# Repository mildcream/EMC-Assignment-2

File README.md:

# Readme

## Smaller headline 

### Smallest headline

* list
* blabla 
* bReadme

## Smaller headline 

### Smallest headline

* list
* blabla 
* babla

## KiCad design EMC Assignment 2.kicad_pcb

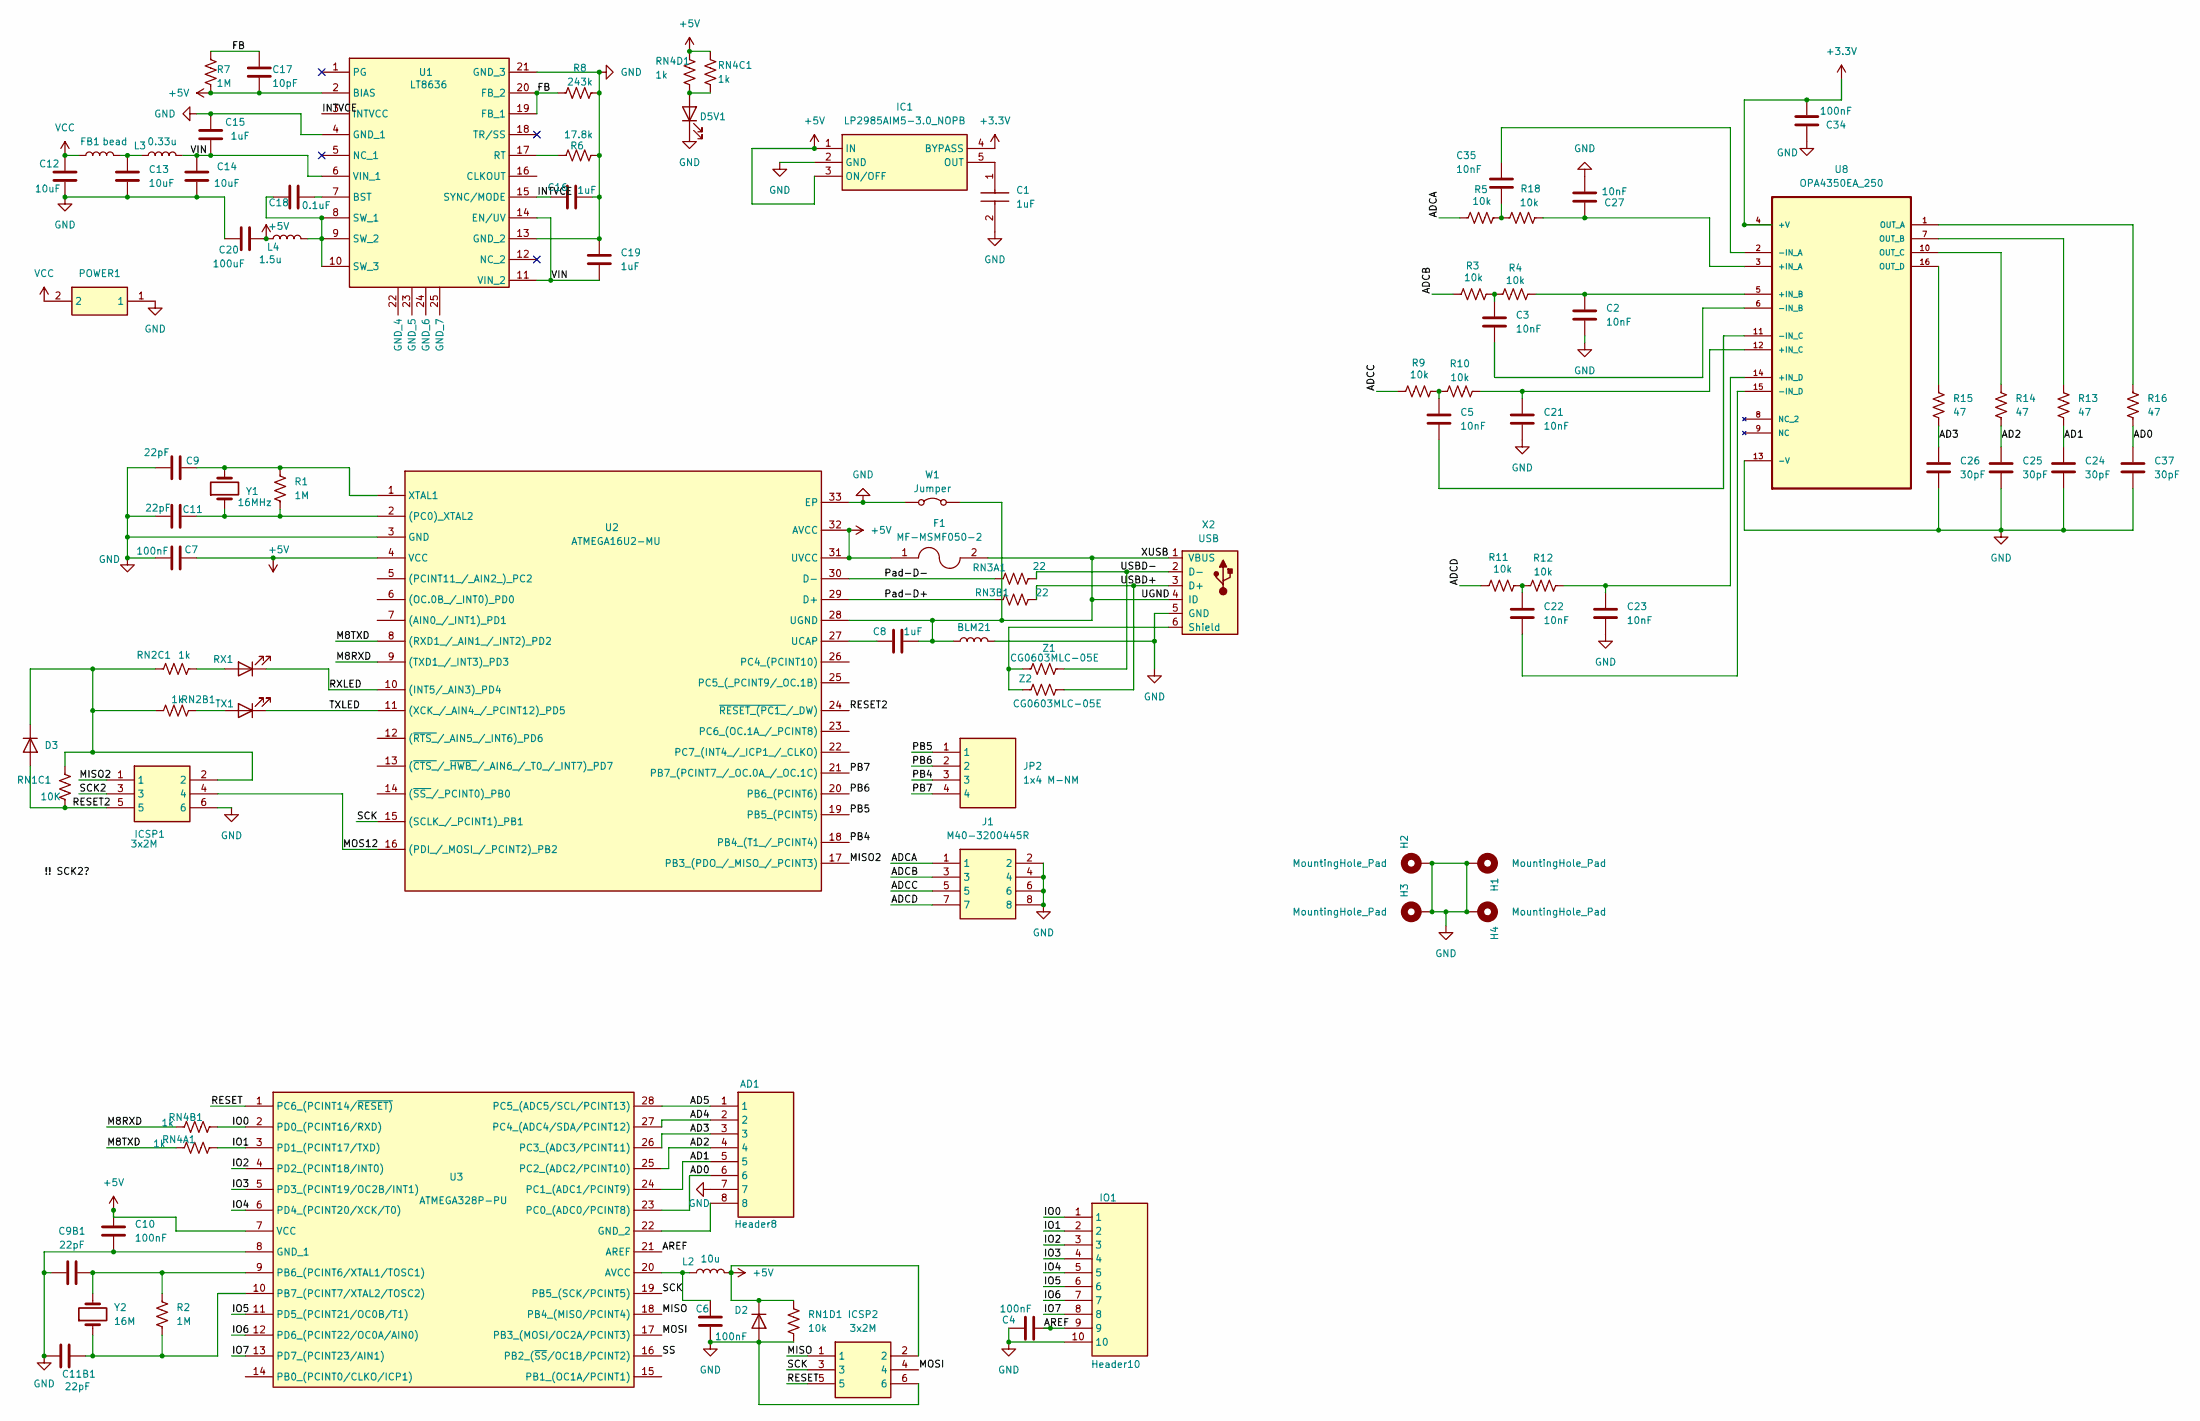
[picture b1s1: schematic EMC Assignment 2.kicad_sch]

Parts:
AD1: Header8; HDRV8W69P0X254_1X8_2032X251X1641P; Mouser Part Number 538-87891-0808
BLM21: L; BLM21AG102BH1J
C1: 1uF; C_0805_2012Metric; Mouser Part Number 581-0805ZC105KAZ2A
C2, C3, C5, C21, C22, C23, C27, C35: 10nF; C_0805_2012Metric
C4, C6, C7, C10: 100nF; C0805
C8, C15, C16, C19: 1uF; C0805
C9, C9B1, C11, C11B1: 22pF; C0805
C12, C13, C14: 10uF; C0805
C17: 10pF; C0805
C18: 0.1uF; C0805
C20: 100uF; C0805
C24, C25, C26, C37: 30pF; C_0805_2012Metric
C34: 100nF; C_0805_2012Metric
D2: 1N4148WT; D_SOD-523
D3: D; D_0805_2012Metric
D5V1: LED; LED_0805_2012Metric
F1: MF-MSMF050-2; FUSC4632X85N; Mouser Part Number 652-MF-MSMF050-2
FB1: bead; L_0805_2012Metric
H1, H2, H3, H4: MountingHole_Pad; MountingHole_2.1mm
IC1: LP2985AIM5-3.0_NOPB; SOT95P280X145-5N; Mouser Part Number 926-2985AIM53.0/NOPB
ICSP1, ICSP2: 3x2M; M225320305R; Mouser Part Number 855-M22-5320305R
IO1: Header10; SHDR10W64P0X250_1X10_2740X575X700P; Manufacturer_Part_Number B10B-XASK-1(LF)(SN)
J1: M40-3200445R; HUSSP8W30P100_2X4_400X320X365P; Mouser Part Number 855-M40-3200445R
JP2: 1x4 M-NM; RHDR4W70P0X254_1X4_1056X250X865P; Mouser Part Number 855-M20-7820446
L2: 10u; L_0805_2012Metric
L3: 0.33u; L_0805_2012Metric
L4: 1.5u; L_0805_2012Metric
POWER1: 3-647166-2; 3-647166-2//; Mouser Part Number 571-3-647166-2
R1, R2, R7: 1M; R_0805_2012Metric
R3, R4, R5, R9, R10, R11, R12, R18: 10k; R_0805_2012Metric
R6: 17.8k; R_0805_2012Metric
R8: 243k; R_0805_2012Metric
R13, R14, R15, R16: 47; R_0805_2012Metric
RN1C1: 10K; R_0805_2012Metric
RN1D1: 10k; R_0805_2012Metric
RN2B1, RN2C1, RN4A1, RN4B1, RN4C1, RN4D1: 1k; R_0805_2012Metric
RN3A1, RN3B1: 22; R_0805_2012Metric
RX1: LED; LED_0805_2012Metric
TX1: LED; LED_0805_2012Metric
U1: LT8636; LT8636HVPBF; Mouser Part Number 584-LT8636HV#PBF
U2: ATMEGA16U2-MU; QFN50P500X500X100-33N-D; Mouser Part Number 556-ATMEGA16U2-MU
U3: ATMEGA328P-PU; DIP794W53P254L3467H457Q28N; Mouser Part Number 556-ATMEGA328P-PU
U8: OPA4350EA_250; OPA4350 SOP64P600X175-16N; MPN OPA4350EA/250
W1: Jumper; SolderJumper-2_P1.3mm_Bridged2Bar_Pad1.0x1.5mm
X2: USB; USB_Micro-B_Wuerth_614105150721_Vertical
Y1: 16MHz; Crystal_SMD_FOX_FE-2Pin_7.5x5.0mm
Y2: 16M; Crystal_SMD_FOX_FE-2Pin_7.5x5.0mm
Z1, Z2: CG0603MLC-05E; VARC1608X55N

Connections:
+3.3V: C34.2, IC1.4 (BYPASS), U8.4 (+V)
+5V: C7.2, C10.1, C17.2, C20.2, D2.1 (K), F1.1, IC1.1 (IN), IC1.3 (ON/OFF), ICSP2.2, L2.2, L4.1, R7.2, RN1D1.1, RN4C1.1, RN4D1.1, U1.2 (BIAS), U2.4 (VCC), U2.31 (UVCC), U2.32 (AVCC), U3.7 (VCC)
/AD0: AD1.6, C37.1, R16.1, U3.23 (PC0_(ADC0/PCINT8))
/AD1: AD1.5, C24.1, R13.1, U3.24 (PC1_(ADC1/PCINT9))
/AD2: AD1.4, C25.1, R14.1, U3.25 (PC2_(ADC2/PCINT10))
/AD3: AD1.3, C26.1, R15.1, U3.26 (PC3_(ADC3/PCINT11))
/AD4: AD1.2, U3.27 (PC4_(ADC4/SDA/PCINT12))
/AD5: AD1.1, U3.28 (PC5_(ADC5/SCL/PCINT13))
/ADCA: J1.1, R5.2
/ADCB: J1.3, R3.2
/ADCC: J1.5, R9.2
/ADCD: J1.7, R11.2
/AREF: C4.2, IO1.9, U3.21 (AREF)
/FB: C17.1, R7.1, R8.1, U1.19 (FB_1), U1.20 (FB_2)
/INTVCE: C16.1, U1.3 (INTVCC), U1.15 (SYNC/MODE)
/IO0: IO1.1, RN4B1.2, U3.2 (PD0_(PCINT16/RXD))
/IO1: IO1.2, RN4A1.2, U3.3 (PD1_(PCINT17/TXD))
/IO2: IO1.3, U3.4 (PD2_(PCINT18/INT0))
/IO3: IO1.4, U3.5 (PD3_(PCINT19/OC2B/INT1))
/IO4: IO1.5, U3.6 (PD4_(PCINT20/XCK/T0))
/IO5: IO1.6, U3.11 (PD5_(PCINT21/OC0B/T1))
/IO6: IO1.7, U3.12 (PD6_(PCINT22/OC0A/AIN0))
/IO7: IO1.8, U3.13 (PD7_(PCINT23/AIN1))
/M8RXD: RN4B1.1, U2.9 ((TXD1_/_INT3)_PD3)
/M8TXD: RN4A1.1, U2.8 ((RXD1_/_AIN1_/_INT2)_PD2)
/MISO: ICSP2.1, U3.18 (PB4_(MISO/PCINT4))
/MISO2: ICSP1.1, U2.17 (PB3_(PDO_/_MISO_/_PCINT3))
/MOS12: ICSP1.4, U2.16 ((PDI_/_MOSI_/_PCINT2)_PB2)
/MOSI: ICSP2.4, U3.17 (PB3_(MOSI/OC2A/PCINT3))
/PB4: JP2.3, U2.18 (PB4_(T1_/_PCINT4))
/PB5: JP2.1, U2.19 (PB5_(PCINT5))
/PB6: JP2.2, U2.20 (PB6_(PCINT6))
/PB7: JP2.4, U2.21 (PB7_(PCINT7_/_OC.0A_/_OC.1C))
/Pad-D+: RN3B1.1, U2.29 (D+)
/Pad-D-: RN3A1.1, U2.30 (D-)
/RESET: ICSP2.5, U3.1 (PC6_(PCINT14/~RESET))
/RESET2: D3.2 (A), ICSP1.5, RN1C1.2, U2.24 (~RESET_(PC1_/_DW))
/RXLED: RX1.1 (K), U2.10 ((INT5/_AIN3)_PD4)
/SCK: ICSP2.3, U2.15 ((SCLK_/_PCINT1)_PB1), U3.19 (PB5_(SCK/PCINT5))
/SCK2: ICSP1.3
/SS: U3.16 (PB2_(~SS/OC1B/PCINT2))
/TXLED: TX1.1 (K), U2.11 ((XCK_/_AIN4_/_PCINT12)_PD5)
/UGND: BLM21.1, C8.2, F1.2, U2.28 (UGND), W1.2 (B), X2.1 (VBUS), X2.4 (ID)
/USBD+: RN3B1.2, X2.3 (D+), Z2.2
/USBD-: RN3A1.2, X2.2 (D-), Z1.2
/VIN: C14.1, C15.2, C19.2, L3.2, U1.6 (VIN_1), U1.11 (VIN_2), U1.14 (EN/UV)
GND: AD1.7, BLM21.2, C1.2, C2.2, C4.1, C6.2, C7.1, C9.1, C9B1.1, C10.2, C11.1, C11B1.1, C12.2, C13.2, C14.2, C15.1, C16.2, C19.1, C20.1, C21.2, C23.2, C24.2, C25.2, C26.2, C27.2, C34.1, C37.2, D2.2 (A), D5V1.1 (K), H1.1, H2.1, H3.1, H4.1, IC1.2 (GND), ICSP1.6, ICSP2.6, IO1.10, J1.2, J1.4, J1.6, J1.8, POWER1.1, R6.2, R8.2, RN1D1.2, U1.4 (GND_1), U1.13 (GND_2), U1.21 (GND_3), U2.3 (GND), U2.33 (EP), U3.8 (GND_1), U8.13 (-V), W1.1 (A), X2.5 (GND)
unnamed: C3.1, R3.1, R4.2
unnamed: C5.1, R9.1, R10.1
unnamed: C13.1, FB1.2, L3.1
unnamed: C22.1, R11.1, R12.1
unnamed: C35.2, R5.1, R18.1
unnamed: D3.1 (K), ICSP1.2, RN1C1.1, RN2B1.1, RN2C1.1
unnamed: D5V1.2 (A), RN4C1.2, RN4D1.2
unnamed: C1.1, IC1.5 (OUT)
unnamed: RN2C1.2, RX1.2 (A)
unnamed: RN2B1.2, TX1.2 (A)
unnamed: C18.2, U1.7 (BST)
unnamed: R6.1, U1.17 (RT)
unnamed: C18.1, L4.2, U1.8 (SW_1), U1.9 (SW_2), U1.10 (SW_3)
unnamed: C11.2, R1.2, U2.2 ((PC0)_XTAL2), Y1.1
unnamed: C8.1, U2.27 (UCAP)
unnamed: C9.2, R1.1, U2.1 (XTAL1), Y1.2
unnamed: C6.1, L2.1, U3.20 (AVCC)
unnamed: AD1.8, U3.22 (GND_2)
unnamed: C9B1.2, R2.1, U3.9 (PB6_(PCINT6/XTAL1/TOSC1)), Y2.2
unnamed: C11B1.2, R2.2, U3.10 (PB7_(PCINT7/XTAL2/TOSC2)), Y2.1
unnamed: C27.1, R18.2, U8.3 (+IN_A)
unnamed: C2.1, R4.1, U8.5 (+IN_B)
unnamed: C21.1, R10.2, U8.12 (+IN_C)
unnamed: C23.1, R12.2, U8.14 (+IN_D)
unnamed: C35.1, U8.2 (-IN_A)
unnamed: C3.2, U8.6 (-IN_B)
unnamed: C5.2, U8.11 (-IN_C)
unnamed: C22.2, U8.15 (-IN_D)
unnamed: R16.2, U8.1 (OUT_A)
unnamed: R13.2, U8.7 (OUT_B)
unnamed: R14.2, U8.10 (OUT_C)
unnamed: R15.2, U8.16 (OUT_D)
unnamed: X2.6 (Shield), Z1.1, Z2.1
VCC: C12.1, FB1.1, POWER1.2

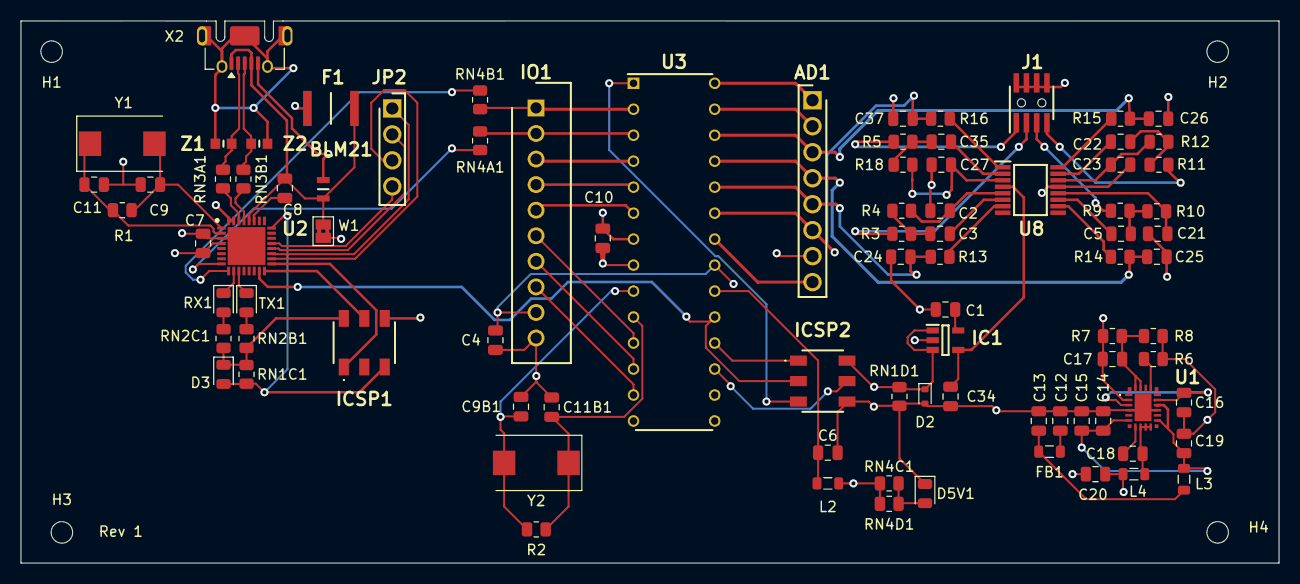
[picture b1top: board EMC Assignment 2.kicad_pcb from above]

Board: 4 copper layers, 123.0 x 53.0 mm, 91 parts (0 on the bottom side), 79 nets.

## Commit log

2024-10-01 Created repo
2024-10-01 Added readme and pcb design markdown files
2024-10-01 updated readme to show off markdown
2024-10-07 Created power supply and ADC schematic
2024-10-11 Final schematic
2024-10-12 Pushed the right build this time o.0
2024-10-12 Some layout around U1 has been done
2024-10-12 Created gitignore file for backup, lock files etc
2024-10-12 U1 layout sketch done
2024-10-12 More stuff done
2024-10-13 Some progress
2024-10-13 more progress, much smaller board
2024-10-15 COmmit before merge to main
2024-10-15 3/4 of blocks done
2024-10-17 WIP, pretty good point
2024-10-17 Pre reannotate test
2024-10-17 Almost all routing done
2024-10-17 Good state
2024-10-19 pcb done
2024-10-19 Fixed majority of DRC issues. Only differential pair needs to be fixed up
2024-10-20 Fixed differential lines with new USB footprint and 3D model. No DRC errors
